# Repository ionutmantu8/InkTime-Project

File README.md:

## Block Diagram
The system is built around the nRF52840 microcontroller, powered from a LiPo battery with USB-C charging, and integrates an e-paper display, IMU, fuel gauge, haptic driver, and three user buttons.

> If the block diagram does not render in your local Markdown viewer, open this file in VS Code and install the **Markdown Preview Mermaid Support** extension.

```mermaid
flowchart LR
    subgraph Power
        USB[USB-C]
        CHG[BQ25180<br/>LiPo Charger]
        BAT[LiPo Battery]
        DCDC[RT6160<br/>DC/DC]
        FG[MAX17048<br/>Fuel Gauge]
    end

    subgraph Core
        MCU[nRF52840]
        ANT[2450AT18B100E<br/>Antenna]
        SWD[SWD Header]
        IMU[BMA421 IMU]
    end

    subgraph Display
        EPDDRV[E-Paper Drive Circuit]
        EPDCONN[503480-2400<br/>E-Paper Connector]
        EPD[E-Paper Display]
    end

    subgraph UI
        BTN[3 Buttons]
        HAPTICDRV[DRV2605<br/>Haptic Driver]
        VIB[Shaker]
    end

    USB --> CHG --> BAT
    BAT --> DCDC
    BAT --> FG
    USB --> MCU
    DCDC --> MCU

    MCU --> ANT
    MCU --> SWD
    MCU <-->|I2C| IMU
    MCU <-->|I2C| FG

    MCU -->|SPI + EPD_CTRL| EPDDRV
    EPDDRV --> EPDCONN --> EPD

    MCU -->|GPIO| BTN
    MCU -->|I2C + HAPTIC_EN| HAPTICDRV
    HAPTICDRV --> VIB
```

## Bill of Materials (BOM)

|Component|JLC Part #|Package|Description|Datasheet|
| :--- | :--- | :--- | :--- | :--- |
|SJ1|N/A|Solder Jumper (Copper feature - leave open)|SMD solder JUMPER|N/A|
|R2, R3, R4|[C3920633](https://www.lcsc.com/product-detail/C3920633.html)|0201|7.68k 0201 Thin Film Surface Mount Fixed Resistor +/-0.5% 0.031W CPF0201D7K68C1|[datasheet](https://wmsc.lcsc.com/wmsc/upload/file/pdf/v2/lcsc/2404081048_TE-Connectivity-CPF0201B511RE1_C3920633.pdf)|
|C23, C27, C34, C42|[C21012218](https://www.lcsc.com/product-detail/C21012218.html)|-|Check availability|[datasheet](https://jlc-prod-smt.oss-eu-central-1.aliyuncs.com/smtDataManualFile/8603520985945550848-C21012218.pdf?response-content-disposition=attachment%3B%20filename%3DC21012218.pdf%3B%20filename%2A%3DUTF-8%27%27C21012218.pdf&x-oss-date=20260407T205848Z&x-oss-expires=1800&x-oss-security-token=CAISgAN1q6Ft5B2yfSjIr5r9Dd2HhJt1xpCRZnzhgHQ0Psp9nrTKiTz2IHhMdHJsAOodtv0%2FmmhT6PkclqRLcbhpcmfjV%2BZHzLB8qYoRtS1%2F4J7b16cNrbH4M4H6aXeirtuwDsz9SNTCALjPD3nPii50x5bjaDymRCbLGJaViJlhHLN1Ow6jdmhpCctxLAlvo9NgFxm3D%2Fu2NQPwiWf9FVdhvhEG6Vly8qOi2MaRmFy8yFTx0b0SvJ%2BjYMrmPctoN9JnSdC5mfdzau3a1TJ84gRD0a5wkaVA1zbDs5bfISEIuUzebreLqY03dV4mOvdqIcMe8qigz88fk%2FfIioH6xyxKOexoSCnFTOiiupCcQLPyao9jLu6iayqViY7QaIOTqQohZmkAMwVOasAsI3Ngh4zF97Qt0cVNkXO9gWfLI8DtuMleWoolCMBMoNHD0eS19jklBdzSlusJRAJJUVBflCeKEaRNSAd3WGhEfM2%2BBt4QT30w5N2u00S8OSMIfXAg5qKWD5sagAGsz%2FZUSUxHdlmxVPmipF%2FTcZWs78wlHh10XRuVSQAFwkjbrT5Hik%2Bt6g43igoBe9p%2FcAdU6beRw%2F0OV8Ul08RsL45K5wTZwHFsbzFcwqB3eAqV0VruhFdx%2FHGC73AK3f%2BS3e6Qh1%2F1xoEQbmetO%2F%2BEcdyt%2BmwKiZrCa5Agq9keuCAA&x-oss-signature-version=OSS4-HMAC-SHA256&x-oss-credential=STS.NYHFg3iDTqRzdZPdta2EQqqak%2F20260407%2Feu-central-1%2Foss%2Faliyun_v4_request&x-oss-signature=20ddec61a1b664f2d44439cb342bbd932d8702b658f2816e0dfb7eb77563430a)|
|EPD_C5|[C9900156064](https://www.lcsc.com/product-detail/C9900156064.html)|201|Generic chip capacitor|[datasheet](https://ds.yuden.co.jp/TYCOMPAS/or/download?pn=MLAST063SCG681JFNA01&fileType=CA)|
|R1_EP_DR|[C3920633](https://www.lcsc.com/product-detail/C3920633.html)|0201|7.68k 0201 Thin Film Surface Mount Fixed Resistor +/-0.5% 0.031W CPF0201D7K68C1|[datasheet](https://wmsc.lcsc.com/wmsc/upload/file/pdf/v2/lcsc/2404081048_TE-Connectivity-CPF0201B511RE1_C3920633.pdf)|
|C15|[C9900156064](https://www.lcsc.com/product-detail/C9900156064.html)|201|Generic chip capacitor|[datasheet](https://ds.yuden.co.jp/TYCOMPAS/or/download?pn=MLAST063SCG681JFNA01&fileType=CA)|
|C5, C7, C8, C12, C19|[C9900156064](https://www.lcsc.com/product-detail/C9900156064.html)|201|Generic chip capacitor|[datasheet](https://ds.yuden.co.jp/TYCOMPAS/or/download?pn=MLAST063SCG681JFNA01&fileType=CA)|
|C11|[C9900156064](https://www.lcsc.com/product-detail/C9900156064.html)|201|Generic chip capacitor|[datasheet](https://ds.yuden.co.jp/TYCOMPAS/or/download?pn=MLAST063SCG681JFNA01&fileType=CA)|
|R2_EP_DR, R9, R_PWR_EPD|[C3920633](https://www.lcsc.com/product-detail/C3920633.html)|0201|7.68k 0201 Thin Film Surface Mount Fixed Resistor +/-0.5% 0.031W CPF0201D7K68C1|[datasheet](https://wmsc.lcsc.com/wmsc/upload/file/pdf/v2/lcsc/2404081048_TE-Connectivity-CPF0201B511RE1_C3920633.pdf)|
|R5, R7, R8|[C3920633](https://www.lcsc.com/product-detail/C3920633.html)|0201|7.68k 0201 Thin Film Surface Mount Fixed Resistor +/-0.5% 0.031W CPF0201D7K68C1|[datasheet](https://wmsc.lcsc.com/wmsc/upload/file/pdf/v2/lcsc/2404081048_TE-Connectivity-CPF0201B511RE1_C3920633.pdf)|
|C1-EP-DR|[C9900156064](https://www.lcsc.com/product-detail/C9900156064.html)|201|Generic chip capacitor|[datasheet](https://ds.yuden.co.jp/TYCOMPAS/or/download?pn=MLAST063SCG681JFNA01&fileType=CA)|
|C24, C39|[C9900179830](https://www.lcsc.com/product-detail/C9900179830.html)|402|0402 (1005 Metric)|N/A|
|L2|[C12669](https://www.lcsc.com/product-detail/C12669.html)|402|Generic chip inductor|[datasheet](https://www.lcsc.com/datasheet/lcsc_datasheet_2304140030_Murata-Electronics-LQG15HS27NJ02D_C12669.pdf)|
|C1, C2, C17, C18|[C9900156064](https://www.lcsc.com/product-detail/C9900156064.html)|201|Generic chip capacitor|[datasheet](https://ds.yuden.co.jp/TYCOMPAS/or/download?pn=MLAST063SCG681JFNA01&fileType=CA)|
|L3|[C12669](https://www.lcsc.com/product-detail/C12669.html)|402|Generic chip inductor|[datasheet](https://www.lcsc.com/datasheet/lcsc_datasheet_2304140030_Murata-Electronics-LQG15HS27NJ02D_C12669.pdf)|
|C3, C4|[C9900156064](https://www.lcsc.com/product-detail/C9900156064.html)|201|Generic chip capacitor|[datasheet](https://ds.yuden.co.jp/TYCOMPAS/or/download?pn=MLAST063SCG681JFNA01&fileType=CA)|
|C29, C30, C31, C32, C37, C38|[C3920633](https://www.lcsc.com/product-detail/C3920633.html)|0201|7.68k 0201 Thin Film Surface Mount Fixed Resistor +/-0.5% 0.031W CPF0201D7K68C1|[datasheet](https://wmsc.lcsc.com/wmsc/upload/file/pdf/v2/lcsc/2404081048_TE-Connectivity-CPF0201B511RE1_C3920633.pdf)|
|EPD_C1, EPD_C2, EPD_C6, EPD_C7, EPD_C8, EPD_C9, EPD_C10, EPD_C11, EPD_C12|[C9900156064](https://www.lcsc.com/product-detail/C9900156064.html)|201|Generic chip capacitor|[datasheet](https://ds.yuden.co.jp/TYCOMPAS/or/download?pn=MLAST063SCG681JFNA01&fileType=CA)|
|R_TYPE_SEL|[C3920633](https://www.lcsc.com/product-detail/C3920633.html)|0201|7.68k 0201 Thin Film Surface Mount Fixed Resistor +/-0.5% 0.031W CPF0201D7K68C1|[datasheet](https://wmsc.lcsc.com/wmsc/upload/file/pdf/v2/lcsc/2404081048_TE-Connectivity-CPF0201B511RE1_C3920633.pdf)|
|SW_DN, SW_ENT, SW_UP|[C569760](https://www.lcsc.com/product-detail/C569760.html)|SMD,3.9x2.9mm|-40℃~+85℃ 1.6N 1.6mm 15V 2.9mm 20mA 3.9mm 500,000 Cycles IP67 J-Lead Rectangular Button SPST Surface Mount,Vertical White With Bracket SMD,3.9x2.9mm Tactile Switches ROHS|[datasheet](https://wmsc.lcsc.com/wmsc/upload/file/pdf/v2/lcsc/2301111010_PANASONIC-EVPAKE31A_C569760.pdf)|
|Q1|[C2564](https://www.lcsc.com/product-detail/C2564.html)|TO-220AB|-55℃~+175℃ 1 P-Channel 180nC@10V 200W 20mΩ@10V 3.4nF 4V 55V 640pF 74A P-Channel TO-220AB MOSFETs ROHS|[datasheet](https://www.lcsc.com/datasheet/lcsc_datasheet_1809041724_Infineon-Technologies-IRF4905PBF_C2564.pdf)|
|C25, C33|[C9900179830](https://www.lcsc.com/product-detail/C9900179830.html)|402|0402 (1005 Metric)|N/A|
|ANT1|[C2917717](https://www.lcsc.com/product-detail/C2917717.html)|1206|-45℃~+125℃ 0.5dBi 1.3mm 1.6mm 100MHz 2.45GHz 2W 3.2mm 50Ω Patch Antenna 1206 Antennas ROHS|[datasheet](https://www.lcsc.com/datasheet/lcsc_datasheet_2404021210_Johanson-Dielectrics-2450AT18B100E_C2917717.pdf)|
|L1|[C12669](https://www.lcsc.com/product-detail/C12669.html)|402|Generic chip inductor|[datasheet](https://www.lcsc.com/datasheet/lcsc_datasheet_2304140030_Murata-Electronics-LQG15HS27NJ02D_C12669.pdf)|
|X2|[C32346](https://www.lcsc.com/product-detail/C32346.html)|SMD3215-2P|-40℃~+85℃ 12.5pF 32.768kHz 70kΩ Crystal Oscillator ±20ppm SMD3215-2P Crystals ROHS|[datasheet](https://www.lcsc.com/datasheet/lcsc_datasheet_2404180925_Seiko-Epson-Q13FC13500004_C32346.pdf)|
|X1|[C9009](https://www.lcsc.com/product-detail/C9009.html)|SMD3225-4P|-40℃~+85℃ 12pF 32MHz Crystal Oscillator ±10ppm ±20ppm SMD3225-4P Crystals ROHS|[datasheet](https://www.lcsc.com/datasheet/lcsc_datasheet_2403291504_YXC-Crystal-Oscillators-X322532MOB4SI_C9009.pdf)|
|R17, R18|[C3920633](https://www.lcsc.com/product-detail/C3920633.html)|0201|7.68k 0201 Thin Film Surface Mount Fixed Resistor +/-0.5% 0.031W CPF0201D7K68C1|[datasheet](https://wmsc.lcsc.com/wmsc/upload/file/pdf/v2/lcsc/2404081048_TE-Connectivity-CPF0201B511RE1_C3920633.pdf)|
|C43|[C9900156064](https://www.lcsc.com/product-detail/C9900156064.html)|201|Generic chip capacitor|[datasheet](https://ds.yuden.co.jp/TYCOMPAS/or/download?pn=MLAST063SCG681JFNA01&fileType=CA)|
|C2-EP-DR|[C9900156064](https://www.lcsc.com/product-detail/C9900156064.html)|201|Generic chip capacitor|[datasheet](https://ds.yuden.co.jp/TYCOMPAS/or/download?pn=MLAST063SCG681JFNA01&fileType=CA)|
|C6, C14, C20, C21|[C9900156064](https://www.lcsc.com/product-detail/C9900156064.html)|201|Generic chip capacitor|[datasheet](https://ds.yuden.co.jp/TYCOMPAS/or/download?pn=MLAST063SCG681JFNA01&fileType=CA)|
|C16|[C9900156064](https://www.lcsc.com/product-detail/C9900156064.html)|201|Generic chip capacitor|[datasheet](https://ds.yuden.co.jp/TYCOMPAS/or/download?pn=MLAST063SCG681JFNA01&fileType=CA)|
|J1|[C122434](https://www.lcsc.com/product-detail/C122434.html)|SMD,P=0.5mm,Surface Mount，Right Angle|FFC & FPC Connectors 0.5mm FPC RA SMT Dual Contact 24Ckt|[datasheet](https://www.molex.com/content/dam/molex/molex-dot-com/products/automated/en-us/salesdrawingpdf/503/503480/5034802400_sd.pdf)|
|R1_USB, R2_USB|[C3920633](https://www.lcsc.com/product-detail/C3920633.html)|0201|7.68k 0201 Thin Film Surface Mount Fixed Resistor +/-0.5% 0.031W CPF0201D7K68C1|[datasheet](https://wmsc.lcsc.com/wmsc/upload/file/pdf/v2/lcsc/2404081048_TE-Connectivity-CPF0201B511RE1_C3920633.pdf)|
|L5|[C1329646](https://www.lcsc.com/product-detail/C1329646.html)|SMD,4.8x4.8mm|1.6A 1.6A 4.7uH 41.4mΩ AEC-Q200 ±30% SMD,4.8x4.8mm Power Inductors ROHS|[datasheet](https://wmsc.lcsc.com/wmsc/upload/file/pdf/v2/lcsc/2304140030_BOURNS-SRR4828A-4R7Y_C1329646.pdf)|
|C9|[C9900156064](https://www.lcsc.com/product-detail/C9900156064.html)|201|Generic chip capacitor|[datasheet](https://ds.yuden.co.jp/TYCOMPAS/or/download?pn=MLAST063SCG681JFNA01&fileType=CA)|
|IC3|[C189517](https://www.lcsc.com/product-detail/C189517.html)|LGA-12(2x2)|Accelerometers Triaxial low-g 12bit Acceleration Sensor|[datasheet](https://www.lcsc.com/datasheet/C189517.pdf)|
|IC1|[C3682423](https://www.lcsc.com/product-detail/C3682423.html)|DSBGA-8(1.1x1.6)|Charger IC Lithium Ion/Polymer, Lithium Iron Phosphate 8-DSBGA (1.6x1.1)|[datasheet](https://www.ti.com/cn/lit/ds/symlink/bq25180.pdf?ts=1775594237116)|
|IC2|[C81079](https://www.lcsc.com/product-detail/C81079.html)|DSBGA-9|Haptic Driver for ERM/LRA with Built-In Library and Smart Loop Architecture|[datasheet](https://www.ti.com/cn/lit/gpn/drv2605)|
|L7|[C5832368](https://www.lcsc.com/product-detail/C5832368.html)|1008|13mΩ 470nH 6.5A 7.5A ±20% 1008 Power Inductors ROHS|[datasheet](https://wmsc.lcsc.com/wmsc/upload/file/pdf/v2/lcsc/2306021632_cjiang--Changjiang-Microelectronics-Tech-FTC252012SR47MBCA_C5832368.pdf)|
|TP (Test Pads)|N/A|N/A|Test pad|N/A|
|J4|[C709357](https://www.lcsc.com/product-detail/C709357.html)|SMD|-40℃~+85℃ 1 10,000 cycles 16P 30V 3A 7.81mm Female Surface Mount, Right Angle Type-C SMD USB Connectors ROHS|[datasheet](https://www.lcsc.com/datasheet/lcsc_datasheet_2404191039_Shenzhen-Kinghelm-Elec-KH-TYPE-C-16P_C709357.pdf)|
|U2|[C2682616](https://www.lcsc.com/product-detail/C2682616.html)|DFN-8-EP(2x2)|-40℃~+85℃ 1 2.5V~4.5V 3uA I2C Lithium Battery DFN-8-EP(2x2) Battery Management ROHS|[datasheet](https://www.lcsc.com/datasheet/lcsc_datasheet_2410121738_Analog-Devices-Inc--Maxim-Integrated-MAX17048G-T10_C2682616.pdf)|
|D2, D4, D5|[C82046](https://www.lcsc.com/product-detail/C82046.html)|SOD-123|ON SEMICONDUCTOR - MBR0530 - DIODE, SCHOTTKY, 0.5A, 30V, SOD-123|[datasheet](https://www.lcsc.com/datasheet/lcsc_datasheet_2304140030_onsemi-MBR0530T1G_C82046.pdf)|
|C10, C13, C22|[C9900156064](https://www.lcsc.com/product-detail/C9900156064.html)|201|Generic chip capacitor|[datasheet](https://ds.yuden.co.jp/TYCOMPAS/or/download?pn=MLAST063SCG681JFNA01&fileType=CA)|
|U1|[C3606653](https://www.lcsc.com/product-detail/C3606653.html)|QFN-48(6x6)|nRF52840|[datasheet](https://www.lcsc.com/datasheet/C3606653.pdf)|
|IC9|[C7065276](https://www.lcsc.com/product-detail/C7065276.html)|WLCSP-15B(2.3x1.4)|Buck-Boost Regulator Positive Output Step-Up/Step-Down I2C DC-DC Controller IC 15-WL-CSP (BSC) (1.4x2.3)|[datasheet](https://wmsc.lcsc.com/wmsc/upload/file/pdf/v2/lcsc/2312271436_Richtek-Tech-RT6160AWSC_C7065276.pdf)|
|Q3|[C469327](https://www.lcsc.com/product-detail/C469327.html)|SOT-323|MOSFET N-Ch 30V 1.5A TrenchFET SC70 Vishay Si1308EDL-T1-GE3 N-channel MOSFET Transistor, 1.5 A, 30 V, 3-Pin SC-70|[datasheet](https://www.lcsc.com/datasheet/lcsc_datasheet_1912202016_Vishay-Intertech-SI1308EDL-T1-GE3_C469327.pdf)|
|J2|[C90533](https://www.lcsc.com/product-detail/C90533.html)|P=1mm|CABLE ADAPTER 6 POS|[datasheet](https://wmsc.lcsc.com/wmsc/upload/file/pdf/v2/lcsc/1810141506_LX-FFC6P1-0mm7CM_C90533.pdf)|
|D3|[C2969755](https://www.lcsc.com/product-detail/C2969755.html)|SOT-23-6L|Low Cap. ESD Protection Auto SOT-23-6 STMicroelectronics USBLC6-2SC6Y, Dual Uni-Directional TVS Diode Array, 6-Pin SOT-23|[datasheet](https://wmsc.lcsc.com/wmsc/upload/file/pdf/v2/lcsc/2211080730_STMicroelectronics-USBLC6-2SC6Y_C2969755.pdf)|

## Hardware Functionality

The hardware platform is built around the **Nordic nRF52840** microcontroller, which acts as the central processing and communication unit of the device. The system integrates power-management circuitry, an inertial sensor, an e-paper display subsystem, a haptic feedback subsystem, USB connectivity, user input buttons, and a debug interface.

### Main hardware blocks

#### 1. Microcontroller – nRF52840
The nRF52840 is the core of the system. It was chosen because it provides:
- low-power operation, suitable for battery-powered wearable devices;
- a rich set of GPIOs;
- integrated USB device support;
- SPI and I2C peripherals for connecting multiple external components;
- SWD debug support;
- BLE capability for future wireless extensions.

The MCU is clocked using:
- a **32 MHz crystal** for the main system clock;
- a **32.768 kHz crystal** for accurate low-power timing.

It also includes the RF matching network and a **2.4 GHz chip antenna** for wireless communication.

---

#### 2. Power subsystem
The device is powered from a **single-cell LiPo battery** and charged through a **USB-C connector**.

The power architecture contains:
- **USB-C connector** for power input and USB communication;
- **USBLC6-2SC6Y** ESD protection for the USB data lines;
- **BQ25180YBGR** battery charger / PMIC for LiPo charging and battery power management;
- **RT6160AWSC** DC/DC converter for generating the regulated supply rail;
- decoupling capacitors and inductors used for filtering and rail stabilization;
- **MAX17048G+T10** fuel gauge for battery level monitoring.

This architecture allows the system to be powered both from USB and from battery, while also monitoring the battery state and keeping energy consumption low.

---

#### 3. E-paper display subsystem
The user interface is based on a **1.54-inch e-paper display**, connected through an FPC connector (**503480-2400**).  
Because the display requires dedicated bias voltages, the design also includes an **e-paper drive circuit** built from passive components, Schottky diodes, MOSFETs and filtering capacitors.

The display subsystem uses:
- **SPI signals** for communication with the MCU;
- several digital control signals:
  - `EPD_CS`
  - `EPD_DC`
  - `EPD_RST`
  - `EPD_BUSY`

The e-paper display was chosen because it has very low static power consumption and is well suited for wearable devices that only update the screen occasionally.

---

#### 4. IMU subsystem
Motion sensing is implemented using the **BMA421 IMU**.  
This sensor communicates with the MCU over **I2C** and provides interrupt outputs:
- `IMU_INT1`
- `IMU_INT2`

The IMU is used for motion/activity awareness and can wake or notify the MCU when specific events occur.

---

#### 5. Battery monitoring
Battery state measurement is handled by the **MAX17048 fuel gauge**, which communicates over **I2C** and provides an `ALERT` line to the MCU.  
This allows the firmware to estimate battery percentage and detect low-battery conditions.

---

#### 6. Haptic feedback
The haptic subsystem is built around the **DRV2605YZFR** haptic driver, connected to the MCU over **I2C**.  
The driver controls the vibration motor (shaker) through:
- `SDA`
- `SCL`
- `HAPTIC_EN`

This solution was chosen because it offloads waveform generation from the microcontroller and allows reliable control of the vibration motor.

---

#### 7. User buttons
The device includes **three buttons**:
- `SW_UP`
- `SW_ENT`
- `SW_DN`

These are connected to dedicated GPIO inputs of the MCU and provide the basic user interface for navigation and interaction.

---

#### 8. Debug and programming
For firmware upload and debugging, the board includes a **TC2030-IDC SWD header**.  
The exposed debug signals are:
- `SWDIO`
- `SWDCLK`
- `SWO`
- `RESET`
- `3.3V`
- `GND`

This header is used during development and testing.

---

## Interfaces used in the design

The design uses the following communication interfaces:

- **USB**
  - used for wired connectivity and battery charging path integration;
  - signals used: `VBUS`, `D+`, `D-`.

- **I2C**
  - shared bus used for:
    - BMA421 IMU
    - MAX17048 fuel gauge
    - DRV2605 haptic driver

- **SPI**
  - used for communication with the e-paper display subsystem

- **GPIO**
  - used for:
    - buttons
    - display control lines
    - interrupt lines
    - enable lines

- **SWD**
  - used for debugging and programming the nRF52840

---

## nRF52840 Pin Usage

Based on the schematic, the following nRF52840 pins are used for the main peripherals:

| nRF52840 Pin | Signal | Connected block | Purpose |
|---|---|---|---|
| P0.13 | D+ | USB-C | USB data line |
| P0.14 | D- | USB-C | USB data line |
| VBUS pin | VBUS | USB-C / charger | USB voltage detection |
| P0.06 | SDA | I2C bus | Shared data line for IMU, fuel gauge and haptic driver |
| P0.07 | SCL | I2C bus | Shared clock line for IMU, fuel gauge and haptic driver |
| P1.13 | MOSI | E-paper display | SPI data output to display |
| P1.15 | SCK | E-paper display | SPI clock |
| P0.17 | EPD_RST | E-paper display | Display reset |
| P0.15 | EPD_BUSY | E-paper display | Busy/status feedback from display |
| P0.16 | EPD_DC | E-paper display | Data/command select |
| P0.05 | EPD_CS | E-paper display | SPI chip select |
| P0.08 | IMU_INT1 | IMU | Interrupt from IMU |
| P1.08 | IMU_INT2 | IMU | Second interrupt from IMU |
| P0.11 | PMIC_INT | BQ25180 | Power-management interrupt |
| P0.24 | ALERT | MAX17048 | Battery fuel gauge alert |
| P0.12 | HAPTIC_EN | DRV2605 | Haptic driver enable/control |
| SWDIO | SWDIO | SWD header | Debug/programming |
| SWDCLK | SWDCLK | SWD header | Debug/programming |
| P0.18 / RESET | RESET | SWD header | Hardware reset |
| P1.09 | SWO | SWD header | Debug trace output |
| ANT pin | RF | Antenna matching network | 2.4 GHz RF connection |

### Why these pins were chosen
The chosen pin mapping follows the functional requirements of the peripherals:
- the dedicated **USB pins** of the nRF52840 are used for `D+` and `D-`;
- the e-paper display uses a mix of **SPI pins** and additional GPIO control lines;
- the sensors and monitoring ICs share the same **I2C bus**, which reduces routing complexity and saves GPIOs;
- interrupt-capable GPIOs are used for `IMU_INT1`, `IMU_INT2`, `PMIC_INT`, and `ALERT`;
- `SWDIO`, `SWDCLK`, `RESET`, and `SWO` are routed to the debug header for easier firmware development.

---

## Power Consumption Considerations

The board was designed with low-power operation in mind.

### Main power-saving choices
- **nRF52840** is a low-power MCU suitable for battery-powered applications.
- **E-paper display** only consumes significant power during refresh; static content does not require continuous display power like an LCD.
- **BQ25180** integrates battery charging and PMIC functionality, reducing the need for discrete always-on circuitry.
- **MAX17048** provides battery estimation with low overhead.
- **I2C shared bus** reduces pin count and simplifies routing.
- The **haptic motor** is driven only when needed.
- Buttons are connected as low-duty-cycle GPIO inputs.
- The external DC/DC stage improves efficiency compared to a purely linear power architecture.

### Qualitative consumption profile
The highest instantaneous consumption occurs during:
- battery charging over USB;
- e-paper refresh;
- vibration motor activation;
- radio activity of the nRF52840.

The lowest consumption mode is expected when:
- the display content is static,
- the MCU is in sleep mode,
- haptic feedback is off,
- no USB power is connected,
- only low-power monitoring remains active.

This makes the platform appropriate for a compact wearable device where energy efficiency matters more than continuous high-performance operation.

## ERC / Schematic Checks

During schematic verification, the project generated a small number of ERC warnings and one input-pin related message. These were reviewed manually before approval.

### Input-pin / single-pin style warnings
Warnings such as:
- `Only INPUT pins on net ...`
- `Only one pin on net ...`

were approved because, according to the project requirements and the lab guidance, these checks can be accepted when the designer has manually verified that the connections are intentional and that no required schematic connections are missing. In this design, the affected nets were inspected and no missing functional connection was identified.

### Power-pin warnings
Warnings of the form:
- `POWER pin ... connected to ...`

were also reviewed manually. After checking the schematic against the intended design, no missing supply rails or broken power connections were found. In addition, this was discussed during the lab, and we were told that such warnings can be approved when the power connectivity is intentional and complete.

## ERC Notes
Some ERC warnings were approved after manual verification. The `Only INPUT pins on net ...` and similar messages were accepted because the affected nets were intentionally connected and no functional connection was missing from the schematic. The power-pin warnings were also checked manually and approved after confirming that the supply rails and power connections were correct.

## DRC Notes
Some DRC warnings were approved in the PCB layout, mainly overlap-related messages such as SMD-via or pad-via overlaps. These were caused intentionally by using via-in-pad / escape routing in dense areas of the board, where this approach was necessary to complete routing in the available space.

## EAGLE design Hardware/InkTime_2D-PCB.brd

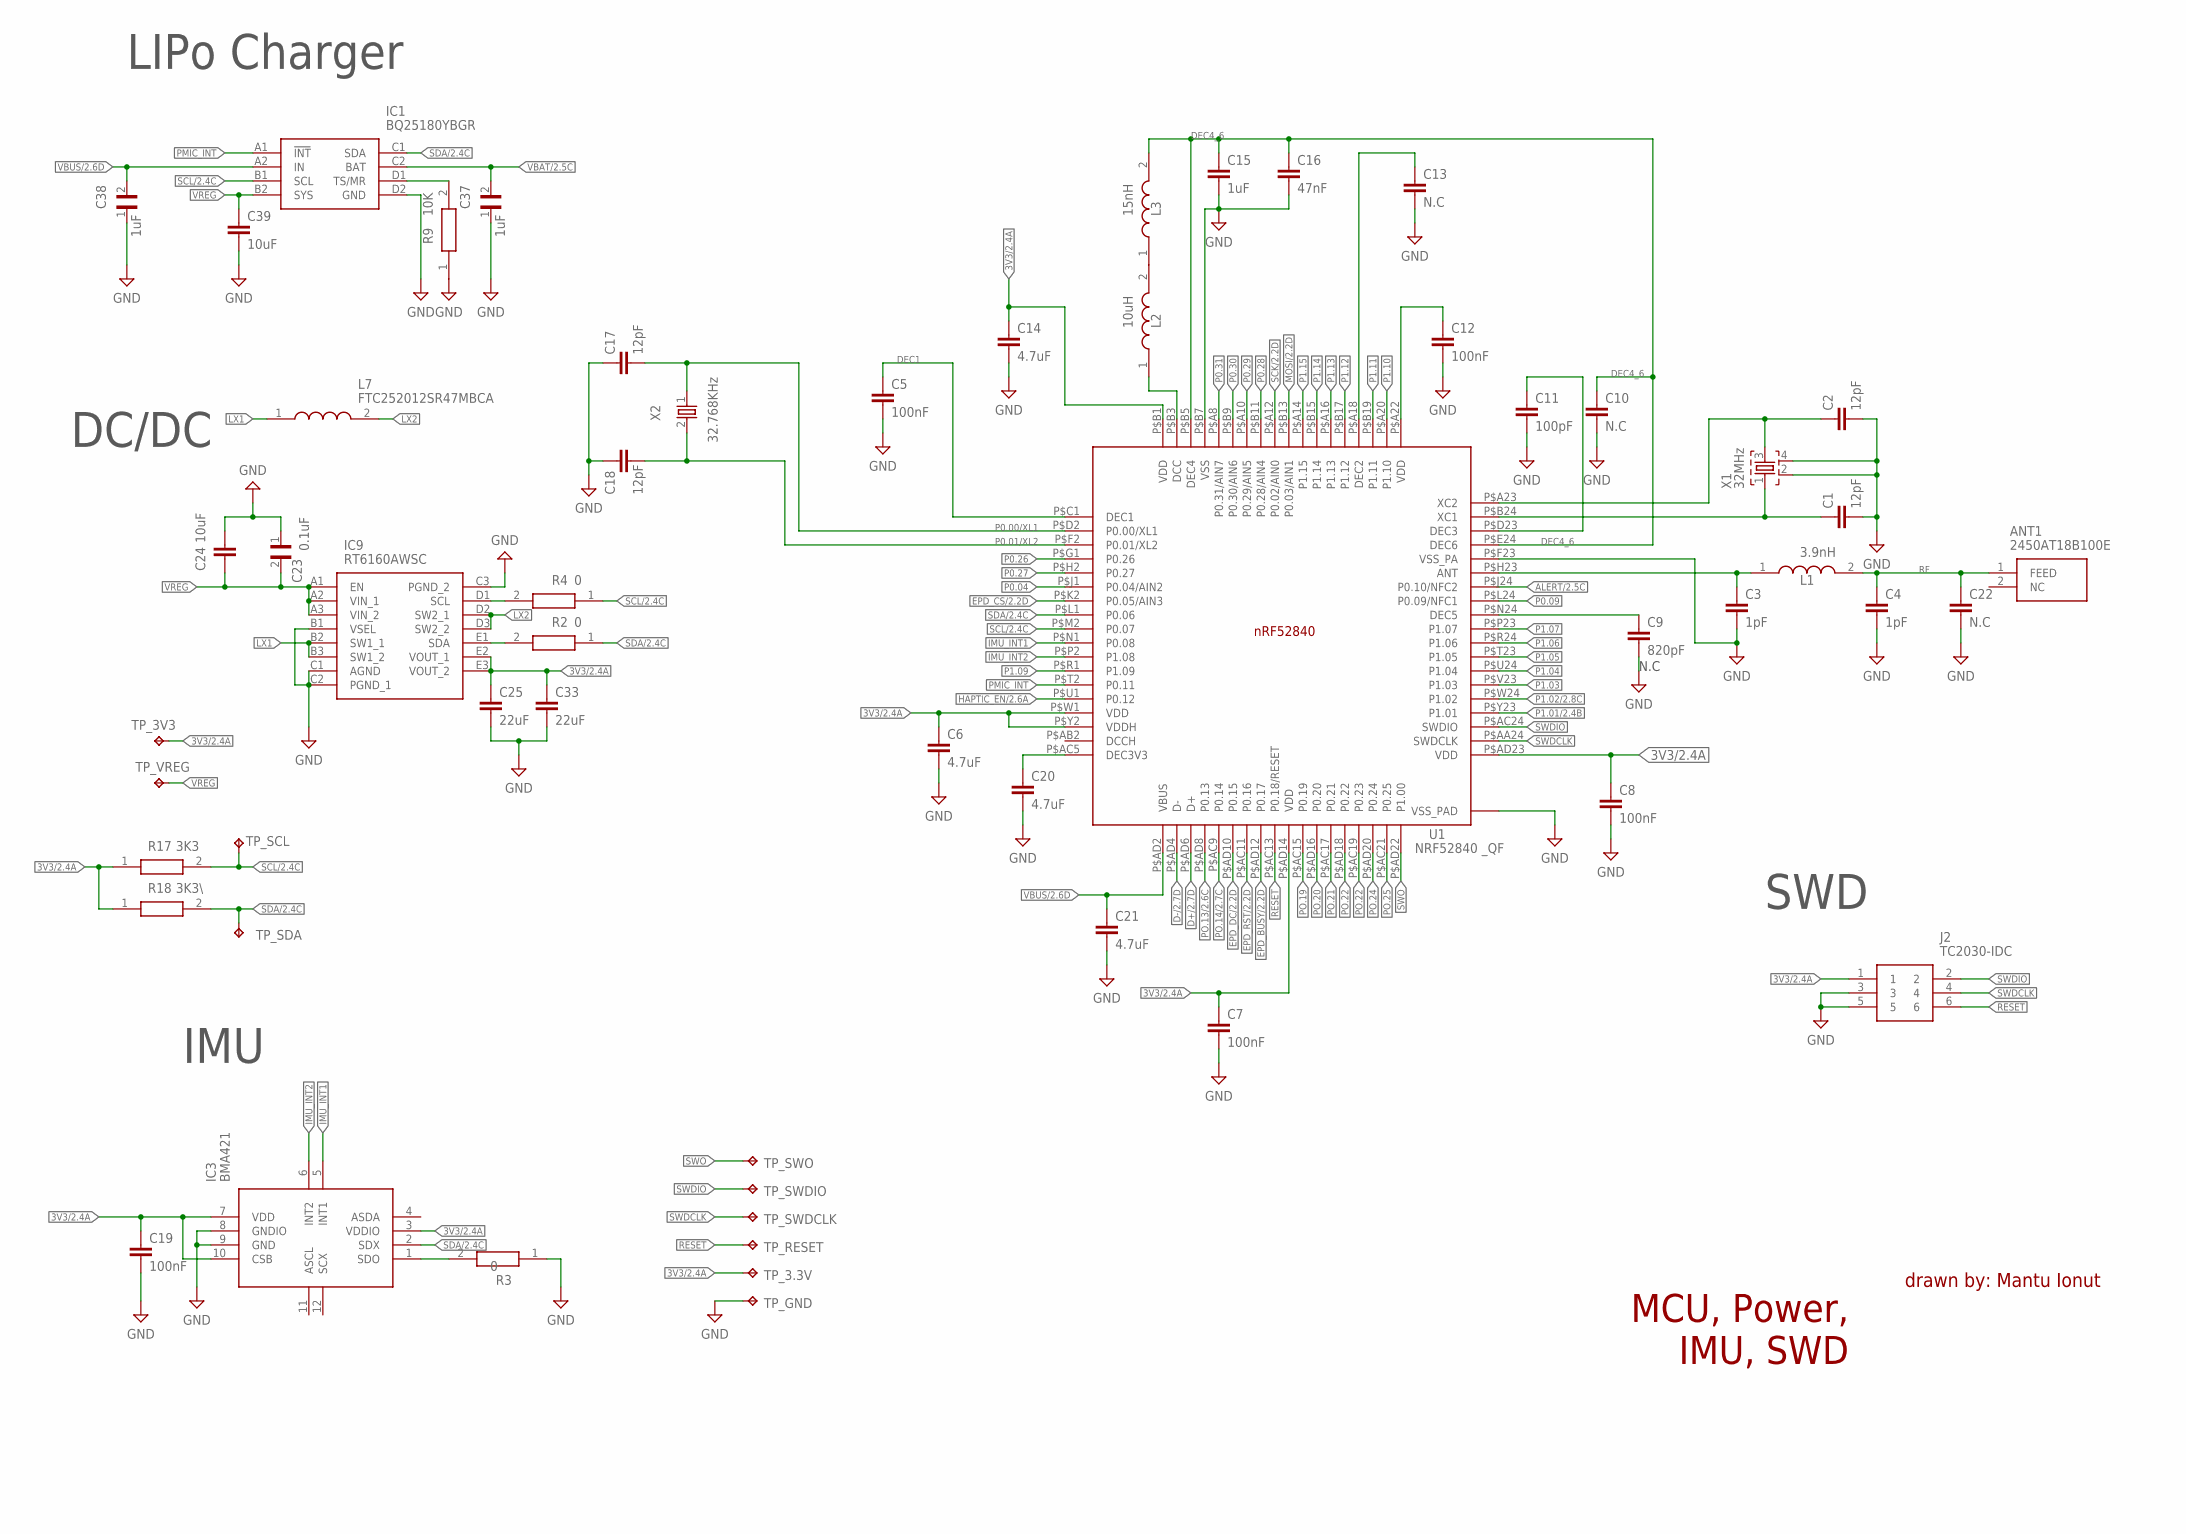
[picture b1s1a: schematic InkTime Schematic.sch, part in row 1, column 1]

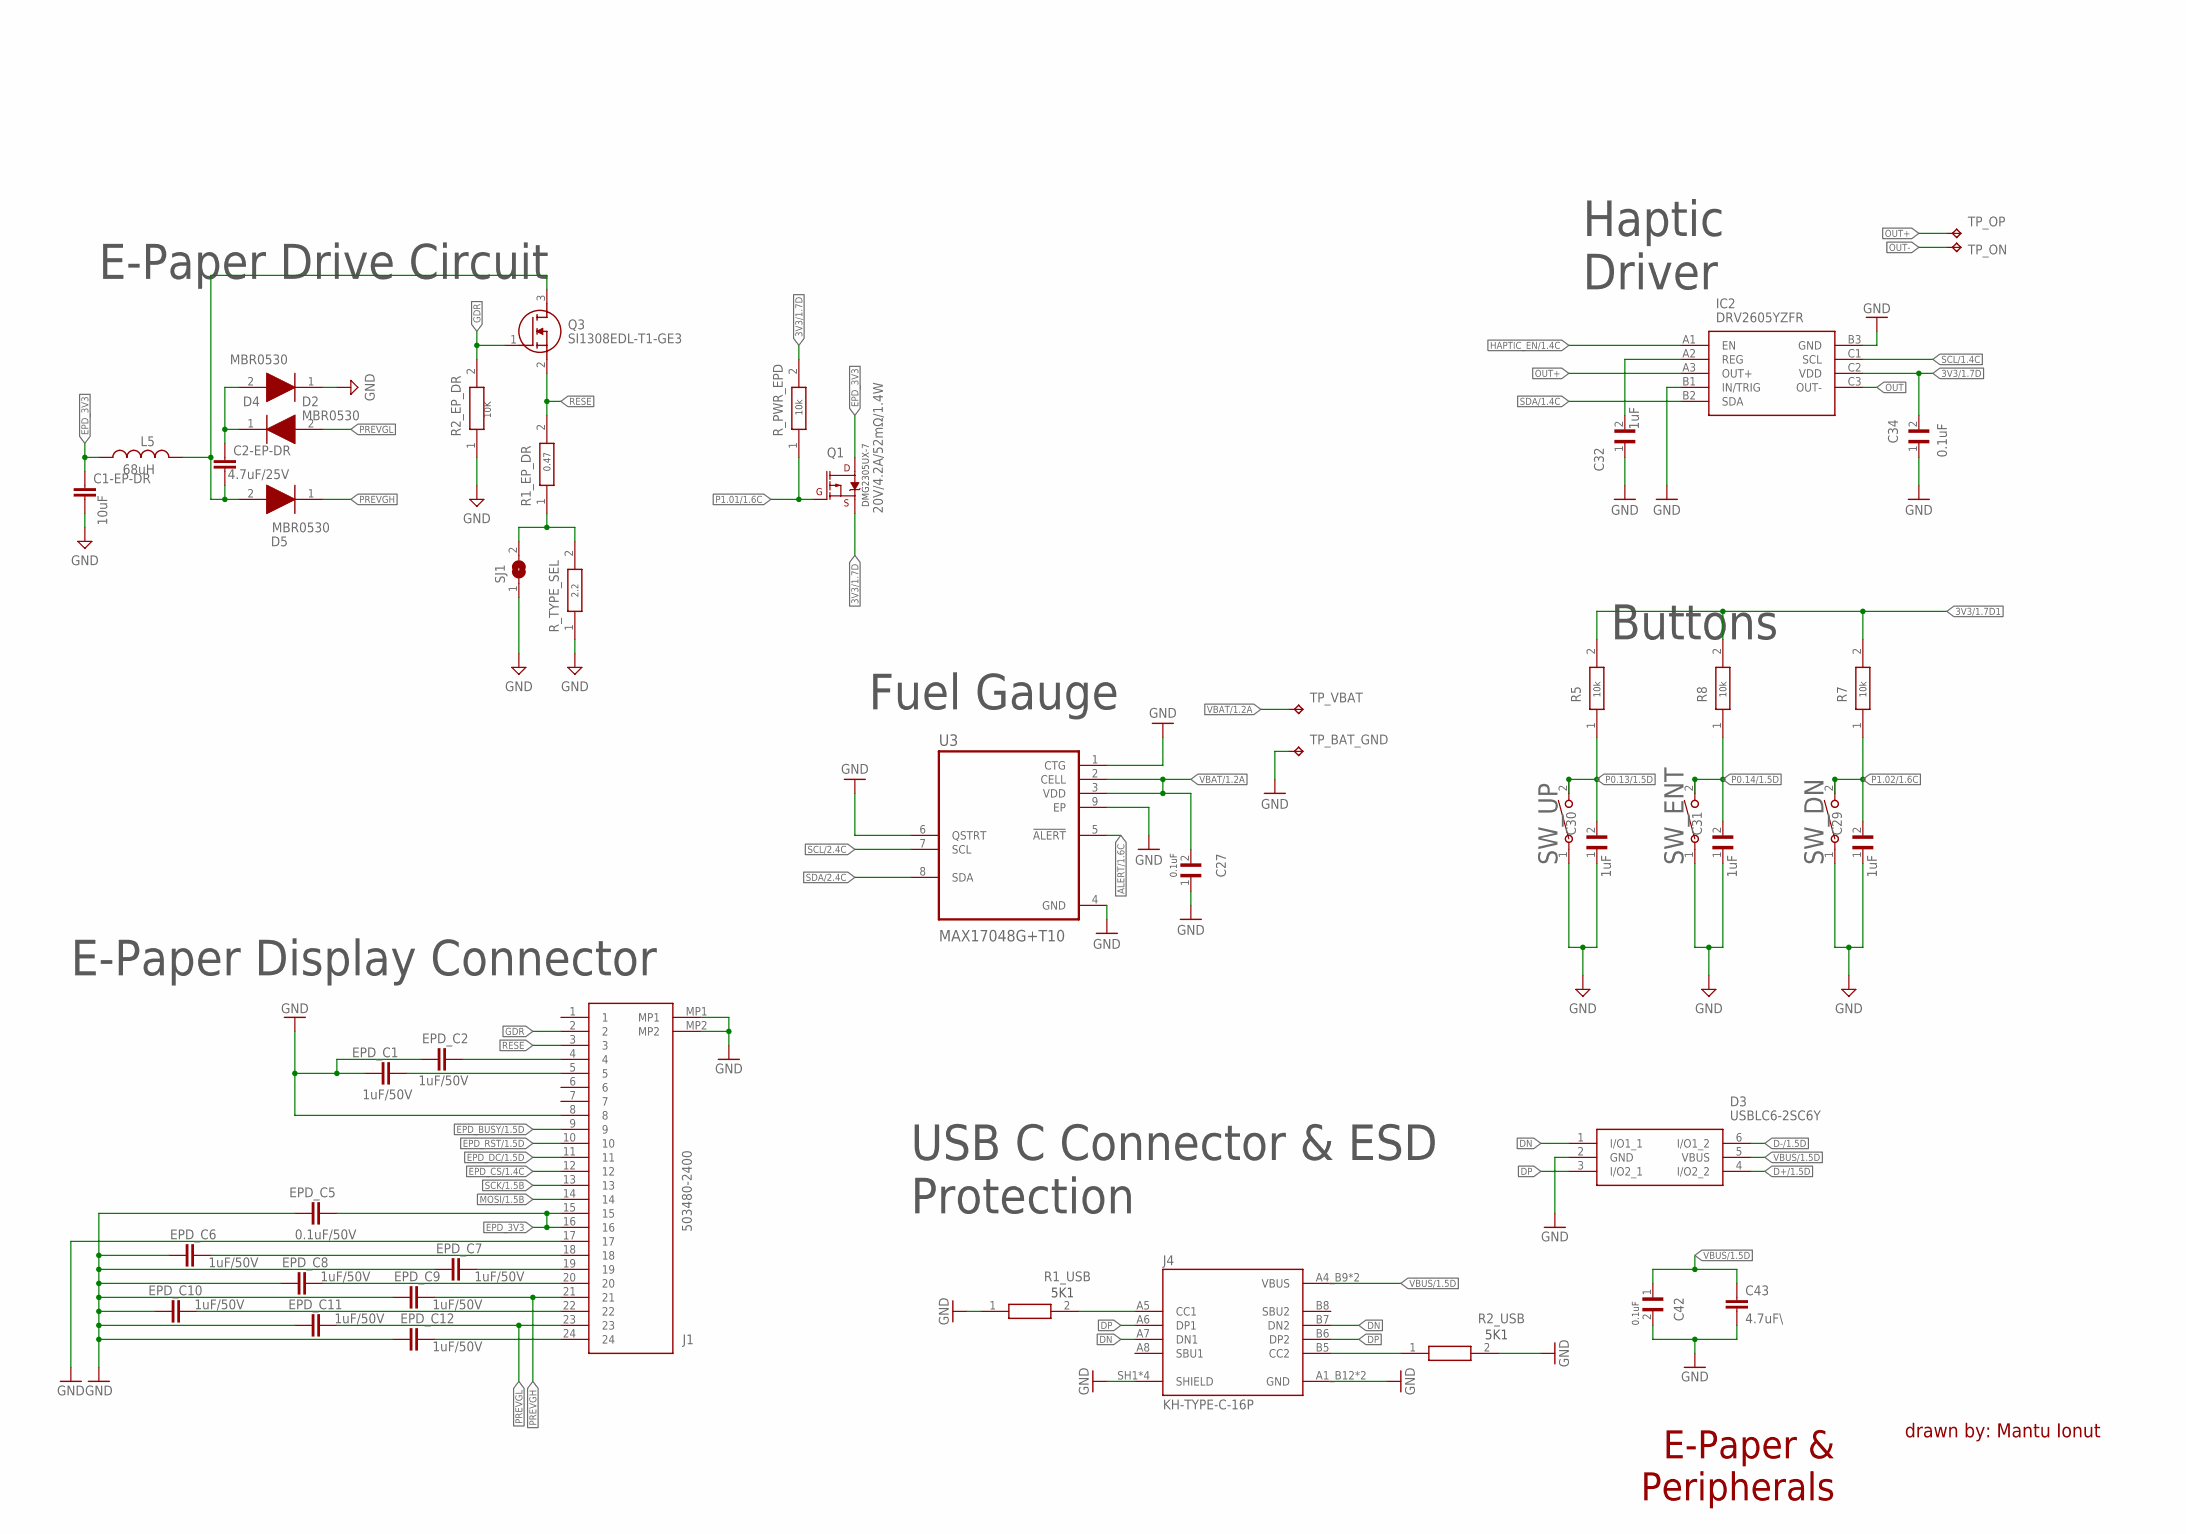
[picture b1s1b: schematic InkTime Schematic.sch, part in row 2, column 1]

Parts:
ANT1: 2450AT18B100E; 2450AT18B100E_ANTC3216X140N
C1, C2, C17, C18: 12pF; NORDIC_NRF_3_RESC0201_L
C1-EP-DR, C24, C39: 10uF; NORDIC_NRF_3_RESC0402_L
C2-EP-DR: 4.7uF/25V; NORDIC_NRF_3_RESC0402_L
C3, C4: 1pF; NORDIC_NRF_3_RESC0201_L
C5, C7, C8, C12, C19: 100nF; NORDIC_NRF_3_RESC0201_L
C6, C14, C20, C21: 4.7uF; NORDIC_NRF_3_RESC0402_L
C9: 820pF; NORDIC_NRF_3_RESC0201_L
C10, C13: N.C; NORDIC_NRF_3_RESC0201_L
C11: 100pF; NORDIC_NRF_3_RESC0201_L
C15: 1uF; NORDIC_NRF_3_RESC0402_L
C16: 47nF; NORDIC_NRF_3_RESC0201_L
C22: N.C; NORDIC_NRF_3_RESC0402_L
C23, C42: 0.1uF; GRM011R60J152KE01L_2_CAPC0201X13N
C25, C33: 22uF; NORDIC_NRF_3_RESC0402_L
C27, C34: 0.1uF; GRM011R60J152KE01L_1_0201
C29, C30, C31, C37, C38: 1uF; GRM011R60J152KE01L_2_CAPC0201X13N
C32: 1uF; GRM011R60J152KE01L_1_0201
C43: 4.7uF\; NORDIC_NRF_3_RESC0402_L
D2, D4, D5: MBR0530; ESP32_C6_LIBRARY_5_SOD3716X135N
D3: USBLC6-2SC6Y; ESP32_C6_LIBRARY_3_SOT95P280X145-6N
EPD_C1, EPD_C2, EPD_C6, EPD_C7, EPD_C8, EPD_C9, EPD_C10, EPD_C11, EPD_C12: 1uF/50V; NORDIC_NRF_3_RESC0402_L
EPD_C5: 0.1uF/50V; NORDIC_NRF_3_RESC0201_L
IC1: BQ25180YBGR; BQ25180YBGR_BGA8C40P2X4_100X155X50
IC2: DRV2605YZFR; DRV2605YZFR_BGA9C50P3X3_144X144X62
IC3: BMA421; BMA423_BMA423
IC9: RT6160AWSC; RT6160AWSC_BGA15C40P3X5_140X230X60
J1: 503480-2400; 503480-2400_5034802400
J2: TC2030-IDC; TC2030-IDC_TC2030IDC
J4: KH-TYPE-C-16P; KH-TYPE-C-16P_KINGHELM_KH-TYPE-C-16P
L1: 3.9nH; MLP2016SR47MT0S1_INDC2016X100N
L2: 10uH; MLP2016SR47MT0S1_INDC2016X100N
L3: 15nH; MLP2016SR47MT0S1_INDC2016X100N
L5: 68uH; NORDIC_NRF_2_RESC0402_L
L7: FTC252012SR47MBCA; MLP2016SR47MT0S1_INDC2016X100N
Q1: 20V/4.2A/52mΩ/1.4W; ESP32_C6_LIBRARY_4_ESP32_C6_LIBRARY_4_ESP32_C6_LIBRARY_4_ES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
Q3: SI1308EDL-T1-GE3; ESP32_C6_LIBRARY_6_SOT65P210X110-3N
R1_EP_DR: 0.47; CPF0201D7K68C1_0201
R1_USB, R2_USB: 5K1; CPF0201D7K68C1_0201
R2, R3, R4: 0; CPF0201D7K68C1_0201
R2_EP_DR, R5, R7, R8, R9: 10K; CPF0201D7K68C1_0201
R17: 3K3; CPF0201D7K68C1_0201
R18: 3K3\; CPF0201D7K68C1_0201
R_PWR_EPD: 10K; CPF0201D7K68C1_0201
R_TYPE_SEL: 2.2; CPF0201D7K68C1_0201
SJ1: 0; ESP32_C6_LIBRARY_7_JUMPER_SJ
SW_DN: 2025-10-22_07-23-44_LIBRARY_EVP-AKE31ASW_EVP-AKE3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; 2025-10-22_07-23-44_LIBRARY_SW_EVP-AKE31A_PAN
SW_ENT: 2025-10-22_07-23-44_LIBRARY_EVP-AKE31ASW_EVP-AKE3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; 2025-10-22_07-23-44_LIBRARY_SW_EVP-AKE31A_PAN
SW_UP: 2025-10-22_07-23-44_LIBRARY_EVP-AKE31ASW_EVP-AKE3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; 2025-10-22_07-23-44_LIBRARY_SW_EVP-AKE31A_PAN
TP_3.3V, TP_3V3: HECTOR_WATCH_1_TPTP20R; HECTOR_WATCH_1_TP20R
TP_BAT_GND: HECTOR_WATCH_1_TPTP20R; HECTOR_WATCH_1_TP20R
TP_GND: HECTOR_WATCH_1_TPTP20R; HECTOR_WATCH_1_TP20R
TP_ON: HECTOR_WATCH_1_TPTP20R; HECTOR_WATCH_1_TP20R
TP_OP: HECTOR_WATCH_1_TPTP20R; HECTOR_WATCH_1_TP20R
TP_RESET: HECTOR_WATCH_1_TPTP20R; HECTOR_WATCH_1_TP20R
TP_SCL: HECTOR_WATCH_1_TPTP20R; HECTOR_WATCH_1_TP20R
TP_SDA: HECTOR_WATCH_1_TPTP20R; HECTOR_WATCH_1_TP20R
TP_SWDCLK: HECTOR_WATCH_1_TPTP20R; HECTOR_WATCH_1_TP20R
TP_SWDIO: HECTOR_WATCH_1_TPTP20R; HECTOR_WATCH_1_TP20R
TP_SWO: HECTOR_WATCH_1_TPTP20R; HECTOR_WATCH_1_TP20R
TP_VBAT: HECTOR_WATCH_1_TPTP20R; HECTOR_WATCH_1_TP20R
TP_VREG: HECTOR_WATCH_1_TPTP20R; HECTOR_WATCH_1_TP20R
U1: NRF52840 _QF; NORDIC_NRF_4_AQFN50P700X700X85_HS-74N
U3: MAX17048G+T10; ESP32_C6_LIBRARY_SON50P200X200X80-9N
X1: 32MHz; NORDIC_NRF_BT-XTAL_2016_N
X2: 32.768KHz; NORDIC_NRF_1_XTAL_3215_N

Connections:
3V3/1.7D: C34.2, IC2.C2 (VDD), Q1.2 (S), R_PWR_EPD.2
3V3/1.7D1: R5.2, R7.2, R8.2
3V3/2.4A: C6.1, C7.1, C8.1, C19.1, C25.1, C33.1, IC3.3 (VDDIO), IC3.7 (VDD), IC3.10 (CSB), IC9.E2 (VOUT_1), IC9.E3 (VOUT_2), J2.1, TP_3.3V.TP, TP_3V3.TP, U1.P$AD14 (VDD), U1.P$AD23 (VDD), U1.P$W1 (VDD), U1.P$Y2 (VDDH)
ALERT/1.6C: U3.5 (!ALERT)
ALERT/2.5C: U1.P$J24 (P0.10/NFC2)
D+/1.5D: D3.4 (I/O2_2)
D+/2.7D: U1.P$AD6 (D+)
D-/1.5D: D3.6 (I/O1_2)
D-/2.7D: U1.P$AD4 (D-)
DEC1: C5.1, U1.P$C1 (DEC1)
DEC4_6: C10.1, C15.1, C16.1, L3.2, U1.P$B5 (DEC4), U1.P$E24 (DEC6)
DN: D3.1 (I/O1_1), J4.A7 (DN1), J4.B7 (DN2)
DP: D3.3 (I/O2_1), J4.A6 (DP1), J4.B6 (DP2)
EPD_3V3: C1-EP-DR.1, EPD_C5.2, J1.15, J1.16, L5.1, Q1.3 (D)
EPD_BUSY/1.5D: J1.9
EPD_BUSY/2.2D: U1.P$AD12 (P0.17)
EPD_CS/1.4C: J1.12
EPD_CS/2.2D: U1.P$K2 (P0.05/AIN3)
EPD_DC/1.5D: J1.11
EPD_DC/2.2D: U1.P$AD10 (P0.15)
EPD_RST/1.5D: J1.10
EPD_RST/2.2D: U1.P$AC11 (P0.16)
GDR: J1.2, Q3.1 (G), R2_EP_DR.2
GND: C1.2, C1-EP-DR.2, C2.2, C3.2, C4.2, C5.2, C6.2, C7.2, C8.2, C9.2, C10.2, C11.2, C12.2, C13.2, C14.2, C15.2, C16.2, C17.1, C18.1, C19.2, C20.2, C21.2, C22.2, C23.1, C24.1, C25.2, C27.1, C29.1, C30.1, C31.1, C32.1, C33.2, C34.1, C37.1, C38.1, C39.2, C42.2, C43.2, D3.2 (GND), D4.1 (K), EPD_C1.1, EPD_C2.1, EPD_C5.1, EPD_C6.1, EPD_C7.1, EPD_C8.1, EPD_C9.1, EPD_C10.1, EPD_C11.1, EPD_C12.1, IC1.D2 (GND), IC2.B1 (IN/TRIG), IC2.B3 (GND), IC3.8 (GNDIO), IC3.9 (GND), IC9.B1 (VSEL), IC9.C1 (AGND), IC9.C2 (PGND_1), IC9.C3 (PGND_2), J1.8, J1.17, J1.MP1, J1.MP2, J2.3, J2.5, J4.A1_B12 (GND), J4.A12_B1 (GND), J4.SH1 (SHIELD), J4.SH2 (SHIELD), J4.SH3 (SHIELD), J4.SH4 (SHIELD), R1_USB.1, R2_EP_DR.1, R2_USB.2, R3.1, R9.1, R_TYPE_SEL.1, SJ1.1, SW_DN.1, SW_ENT.1, SW_UP.1, TP_BAT_GND.TP, TP_GND.TP, U1.P$74 (VSS_PAD), U1.P$75 (VSS_PAD), U1.P$76 (VSS_PAD), U1.P$77 (VSS_PAD), U1.P$78 (VSS_PAD), U1.P$79 (VSS_PAD), U1.P$80 (VSS_PAD), U1.P$81 (VSS_PAD), U1.P$82 (VSS_PAD), U1.P$83 (VSS_PAD), U1.P$84 (VSS_PAD), U1.P$85 (VSS_PAD), U1.P$86 (VSS_PAD), U1.P$87 (VSS_PAD), U1.P$88 (VSS_PAD), U1.P$89 (VSS_PAD), U1.P$90 (VSS_PAD), U1.P$B7 (VSS), U1.P$F23 (VSS_PA), U3.1 (CTG), U3.4 (GND), U3.6 (QSTRT), U3.9 (EP), X1.2, X1.4
HAPTIC_EN/1.4C: IC2.A1 (EN)
HAPTIC_EN/2.6A: U1.P$U1 (P0.12)
IMU_INT1: IC3.5 (INT1), U1.P$N1 (P0.08)
IMU_INT2: IC3.6 (INT2), U1.P$P2 (P1.08)
LX1: IC9.B2 (SW1_1), IC9.B3 (SW1_2), L7.1
LX2: IC9.D2 (SW2_1), IC9.D3 (SW2_2), L7.2
MOSI/1.5B: J1.14
MOSI/2.2D: U1.P$B13 (P0.03/AIN1)
unnamed: C11.1, U1.P$D23 (DEC3)
unnamed: C3.1, L1.1, U1.P$H23 (ANT)
unnamed: C1.1, U1.P$B24 (XC1), X1.1
unnamed: C2.1, U1.P$A23 (XC2), X1.3
unnamed: C20.1, U1.P$AC5 (DEC3V3)
unnamed: C9.1, U1.P$N24 (DEC5)
unnamed: C14.1, U1.P$B1 (VDD)
unnamed: L2.1, U1.P$B3 (DCC)
unnamed: L2.2, L3.1
unnamed: C13.1, U1.P$A18 (DEC2)
unnamed: C12.1, U1.P$A22 (VDD)
unnamed: IC3.1 (SDO), R3.2
unnamed: IC9.D1 (SCL), R4.2
unnamed: IC9.E1 (SDA), R2.2
unnamed: R17.1, R18.1
unnamed: IC1.D1 (TS/MR), R9.2
unnamed: C2-EP-DR.2, D5.2 (A), L5.2, Q3.3 (D)
unnamed: C2-EP-DR.1, D2.1 (K), D4.2 (A)
unnamed: R1_EP_DR.1, R_TYPE_SEL.2, SJ1.2
unnamed: EPD_C2.2, J1.4
unnamed: EPD_C1.2, J1.5
unnamed: EPD_C6.2, J1.18
unnamed: EPD_C7.2, J1.19
unnamed: EPD_C8.2, J1.20
unnamed: EPD_C10.2, J1.22
unnamed: EPD_C12.2, J1.24
unnamed: C32.2, IC2.A2 (REG)
unnamed: J4.A5 (CC1), R1_USB.2
unnamed: J4.B5 (CC2), R2_USB.1
OUT: IC2.C3 (OUT-)
OUT+: IC2.A3 (OUT+), TP_OP.TP
OUT-: TP_ON.TP
P0.00/XL1: C17.2, U1.P$D2 (P0.00/XL1), X2.1
P0.01/XL2: C18.2, U1.P$F2 (P0.01/XL2), X2.2
P0.04: U1.P$J1 (P0.04/AIN2)
P0.09: U1.P$L24 (P0.09/NFC1)
P0.13/1.5D: C30.2, R5.1, SW_UP.2
P0.14/1.5D: C31.2, R8.1, SW_ENT.2
P0.26: U1.P$G1 (P0.26)
P0.27: U1.P$H2 (P0.27)
P0.28: U1.P$B11 (P0.28/AIN4)
P0.29: U1.P$A10 (P0.29/AIN5)
P0.30: U1.P$B9 (P0.30/AIN6)
P0.31: U1.P$A8 (P0.31/AIN7)
P1.01/1.6C: Q1.1 (G), R_PWR_EPD.1
P1.01/2.4B: U1.P$Y23 (P1.01)
P1.02/1.6C: C29.2, R7.1, SW_DN.2
P1.02/2.8C: U1.P$W24 (P1.02)
P1.03: U1.P$V23 (P1.03)
P1.04: U1.P$U24 (P1.04)
P1.05: U1.P$T23 (P1.05)
P1.06: U1.P$R24 (P1.06)
P1.07: U1.P$P23 (P1.07)
P1.09: U1.P$R1 (P1.09)
P1.10: U1.P$A20 (P1.10)
P1.11: U1.P$B19 (P1.11)
P1.12: U1.P$B17 (P1.12)
P1.13: U1.P$A16 (P1.13)
P1.14: U1.P$B15 (P1.14)
P1.15: U1.P$A14 (P1.15)
PMIC_INT: IC1.A1 (!INT), U1.P$T2 (P0.11)
PO.13/2.6C: U1.P$AD8 (P0.13)
PO.14/2.7C: U1.P$AC9 (P0.14)
PO.19: U1.P$AC15 (P0.19)
PO.20: U1.P$AD16 (P0.20)
PO.21: U1.P$AC17 (P0.21)
PO.22: U1.P$AC19 (P0.23)
PO.24: U1.P$AD20 (P0.24)
PO.25: U1.P$AC21 (P0.25)
PREVGH: D5.1 (K), EPD_C9.2, J1.21
PREVGL: D2.2 (A), EPD_C11.2, J1.23
RESE: J1.3, Q3.2 (S), R1_EP_DR.2
RESET: J2.6, TP_RESET.TP, U1.P$AC13 (P0.18/RESET)
RF: ANT1.1 (FEED), C4.1, C22.1, L1.2
SCK/1.5B: J1.13
SCK/2.2D: U1.P$A12 (P0.02/AIN0)
SCL/1.4C: IC2.C1 (SCL)
SCL/2.4C: IC1.B1 (SCL), R4.1, R17.2, TP_SCL.TP, U1.P$M2 (P0.07), U3.7 (SCL)
SDA/1.4C: IC2.B2 (SDA)
SDA/2.4C: IC1.C1 (SDA), IC3.2 (SDX), R2.1, R18.2, TP_SDA.TP, U1.P$L1 (P0.06), U3.8 (SDA)
SWDCLK: J2.4, TP_SWDCLK.TP, U1.P$AA24 (SWDCLK)
SWDIO: J2.2, TP_SWDIO.TP, U1.P$AC24 (SWDIO)
SWO: TP_SWO.TP, U1.P$AD22 (P1.00)
VBAT/1.2A: C27.2, TP_VBAT.TP, U3.2 (CELL), U3.3 (VDD)
VBAT/2.5C: C37.2, IC1.C2 (BAT)
VBUS/1.5D: C42.1, C43.1, D3.5 (VBUS), J4.A4_B9 (VBUS), J4.A9_B4 (VBUS)
VBUS/2.6D: C21.1, C38.2, IC1.A2 (IN), U1.P$AD2 (VBUS)
VREG: C23.2, C24.2, C39.1, IC1.B2 (SYS), IC9.A1 (EN), IC9.A2 (VIN_1), IC9.A3 (VIN_2), TP_VREG.TP

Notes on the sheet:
SWD
IMU
DC/DC
LIPo Charger
E-Paper Drive Circuit
0.47
2.2
10K
DMG2305UX-7
10k
E-Paper Display Connector
Buttons
Haptic Driver
Fuel Gauge
0.1uF
5K1
USB C Connector & ESD Protection
MCU, Power, IMU, SWD
E-Paper & Peripherals
drawn by: Mantu Ionut
N.C

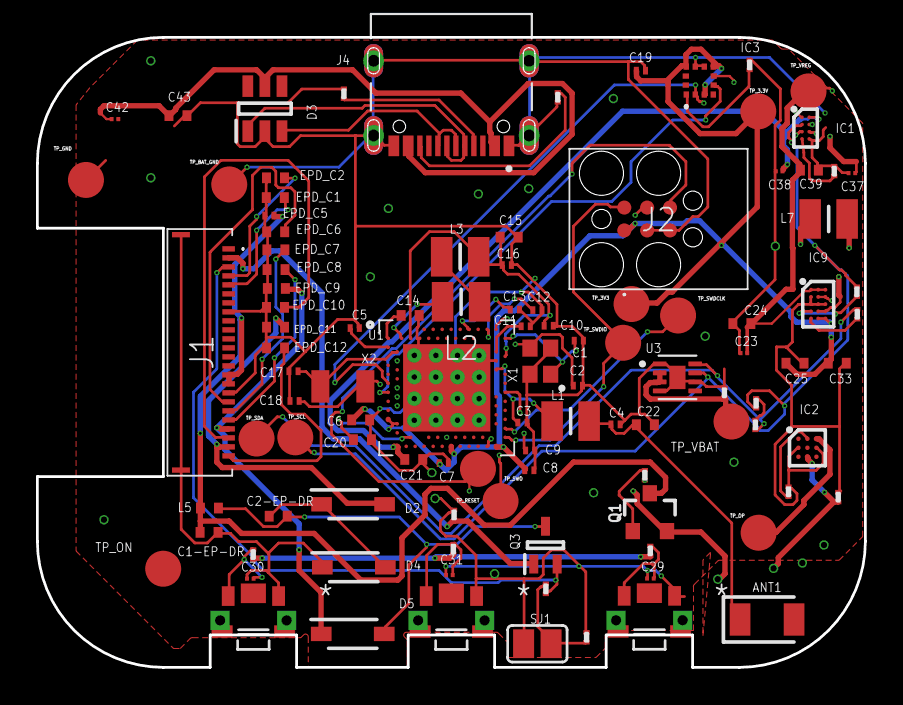
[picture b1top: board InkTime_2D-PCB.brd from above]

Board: 4 copper layers, 46.0 x 35.0 mm, 105 parts (0 on the bottom side), 66 nets.

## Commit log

2026-03-20 Added project structure
2026-03-20 Add the rest of the project structure
2026-04-10 Add LICENSE file
2026-04-10 Added the entire project
2026-04-10 Remove DS_Store file
2026-04-13 Reuploaded Bom and Cpl files as they had a problem where they couldn't be opened when transformed to .csv
2026-04-16 Completed README to have links to datasheet and place to buy
2026-04-17 Completed README, added 3D models to all the components and solved a problem with the ground plane
2026-04-17 Removed unnecesary files
2026-04-17 Remove gitignore
2026-04-17 Remove Ds_Store
2026-04-20 Added Via Stiching to GND planes
2026-04-22 Modified Complete Device
2026-04-22 Modified PCB

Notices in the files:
parts and their libraries:
InkTime_v5: COPYRIGHT: Copyright (C) 2025 Ultra Librarian. All rights reserved.
